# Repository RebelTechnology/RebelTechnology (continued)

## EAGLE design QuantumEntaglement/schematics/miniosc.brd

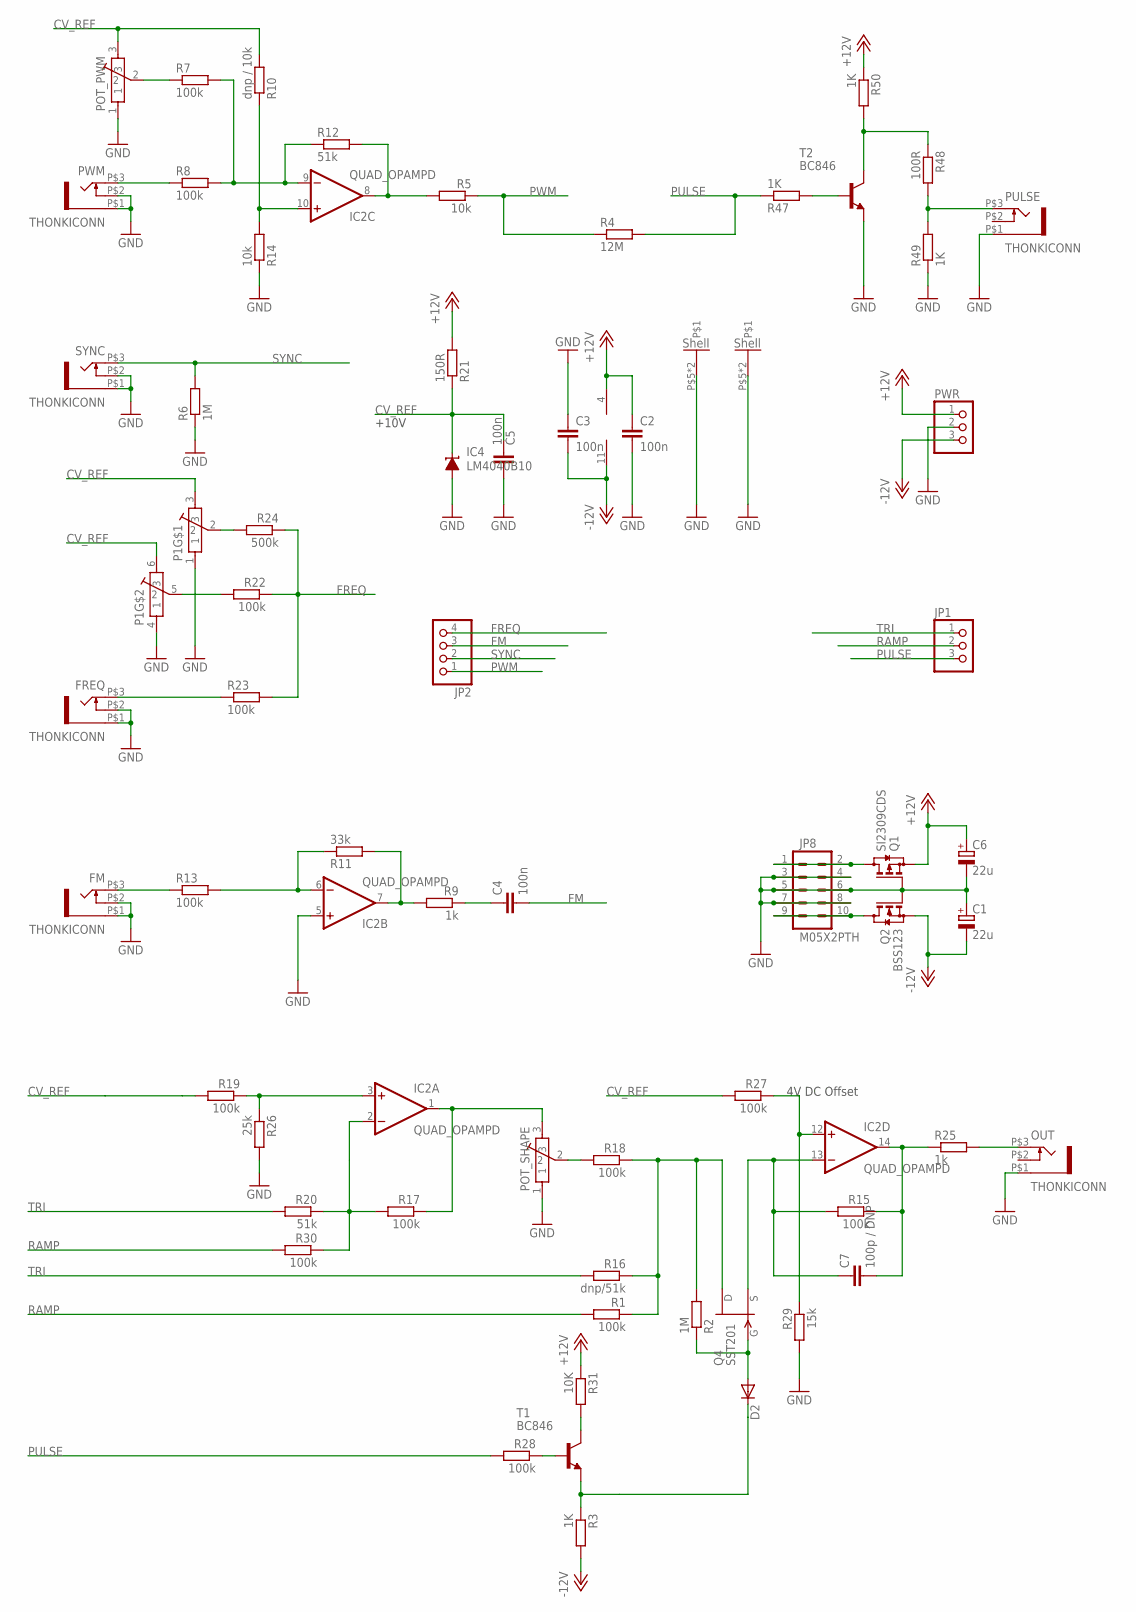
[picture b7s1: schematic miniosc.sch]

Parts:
C1, C6: 22u; CPOL-5
C2, C3, C4, C5: 100n; C0603
C7: 100p / DNP; C0603
D2: DIODE; DIODE-0805
FM: THONKICONN
FREQ: THONKICONN
IC2: QUAD_OPAMPD; SO14
IC4: LM4040B10; DBZ_R-PDSO-G3
JP1: PINHD-1X3; 1X03
JP2: PINHD-1X4; 1X04
JP8: M05X2PTH; AVR_ICSP
OUT: THONKICONN
P1: POT-BOURNS-PTD902
POT_PWM: POT-ALPS-RK09L1140
POT_SHAPE: POT-ALPS-RK09L1140
PULSE: THONKICONN
PWM: THONKICONN
PWR: PINHD-1X3; 1X03
Q1: SI2309CDS; SOT23
Q2: BSS123; SOT23
Q4: SST201; SOT23
R1, R7, R8, R13, R15, R17, R18, R19, R22, R23, R27, R28, R30: 100k; 0603
R2, R6: 1M; 0603
R3, R47, R49, R50: 1K; 0603
R4: 12M; 0603
R5, R14: 10k; 0603
R9, R25: 1k; 0603
R10: dnp / 10k; 0603
R11: 33k; 0603
R12, R20: 51k; 0603
R16: dnp/51k; 0603
R21: 150R; 0603
R24: 500k; 0603
R26: 25k; 0603
R29: 15k; 0603
R31: 10K; 0603
R48: 100R; 0603
SYNC: THONKICONN
T1, T2: BC846; SOT23

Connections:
+12V: C2.1, C6.+, IC2.4 (V+), PWR.1, Q1.2 (S), R21.2, R31.1, R50.1
-12V: C1.-, C3.2, IC2.11 (V-), PWR.3, Q2.2 (S), R3.2
CV_REF: C5.1, IC4.1 (C), P1.3, P1.6 (3), POT_PWM.3, R10.2, R19.2, R21.1, R27.2
FM: C4.2, JP2.3
FREQ: JP2.4, R22.1, R23.2, R24.1
GND: C1.+, C2.2, C3.1, C5.2, C6.-, FM.P$1 (5), FM.P$2 (4), FREQ.P$1 (5), FREQ.P$2 (4), IC2.5 (+IN), IC4.2 (A), JP8.3, JP8.4, JP8.5, JP8.6, JP8.7, JP8.8, OUT.P$1 (5), P1.1, P1.4 (1), POT_PWM.1, POT_PWM.P$5, POT_PWM.P$6, POT_SHAPE.1, POT_SHAPE.P$5, POT_SHAPE.P$6, PULSE.P$1 (5), PWM.P$1 (5), PWM.P$2 (4), PWR.2, Q1.1 (G), Q2.1 (G), R6.1, R14.1, R26.2, R29.2, R49.1, SYNC.P$1 (5), SYNC.P$2 (4), T2.2 (E)
unnamed: R31.2, T1.3 (C)
unnamed: PWM.P$3 (3), R8.1
unnamed: FREQ.P$3 (3), R23.1
unnamed: C7.1, IC2.13 (-IN), Q4.2 (S), R15.2
unnamed: IC2.9 (-IN), R7.2, R8.2, R12.1
unnamed: IC2.10 (+IN), R10.1, R14.2
unnamed: JP8.9, JP8.10, Q2.3 (D)
unnamed: P1.2, R24.2
unnamed: PULSE.P$3 (3), R48.2, R49.2
unnamed: IC2.1 (OUT), POT_SHAPE.3, R17.1
unnamed: JP8.1, JP8.2, Q1.3 (D)
unnamed: P1.5 (2), R22.2
unnamed: IC2.2 (-IN), R17.2, R20.1, R30.1
unnamed: C7.2, IC2.14 (OUT), R15.1, R25.1
unnamed: IC2.3 (+IN), R19.1, R26.1
unnamed: IC2.12 (+IN), R27.1, R29.1
unnamed: FM.P$3 (3), R13.1
unnamed: IC2.6 (-IN), R11.1, R13.2
unnamed: OUT.P$3 (3), R25.2
unnamed: IC2.7 (OUT), R9.2, R11.2
unnamed: C4.1, R9.1
unnamed: Q4.1 (D), R1.1, R2.2, R16.1, R18.1
unnamed: D2.C, R3.1, T1.2 (E)
unnamed: POT_PWM.2, R7.1
unnamed: IC2.8 (OUT), R5.2, R12.2
unnamed: R28.1, T1.1 (B)
unnamed: POT_SHAPE.2, R18.2
unnamed: D2.A, Q4.3 (G), R2.1
unnamed: R47.2, T2.1 (B)
unnamed: R48.1, R50.2, T2.3 (C)
PULSE: JP1.3, R4.2, R28.2, R47.1
PWM: JP2.1, R4.1, R5.1
RAMP: JP1.2, R1.2, R30.2
SYNC: JP2.2, R6.2, SYNC.P$3 (3)
TRI: JP1.1, R16.2, R20.2

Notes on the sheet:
+10V
4V DC Offset

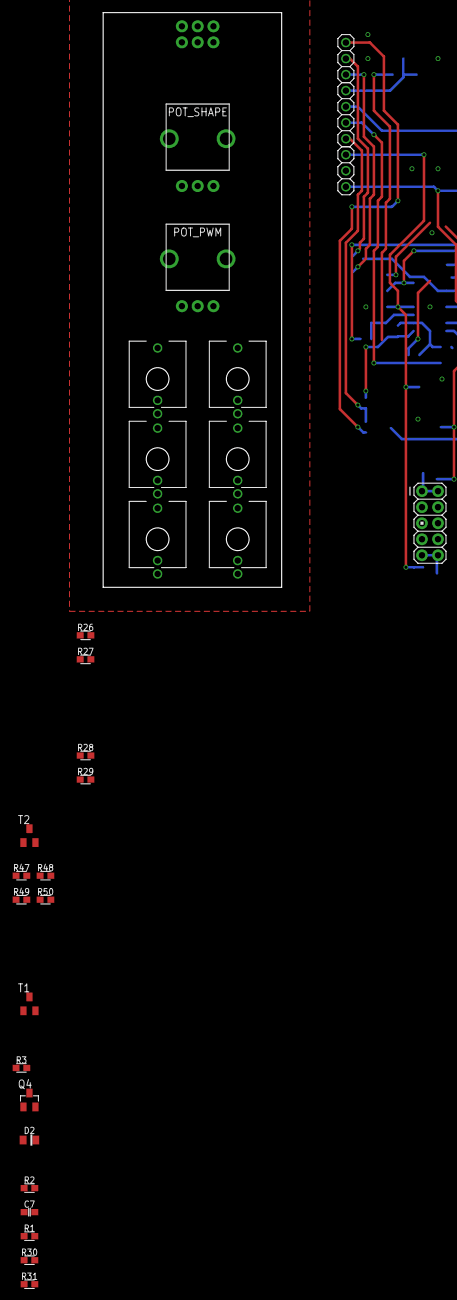
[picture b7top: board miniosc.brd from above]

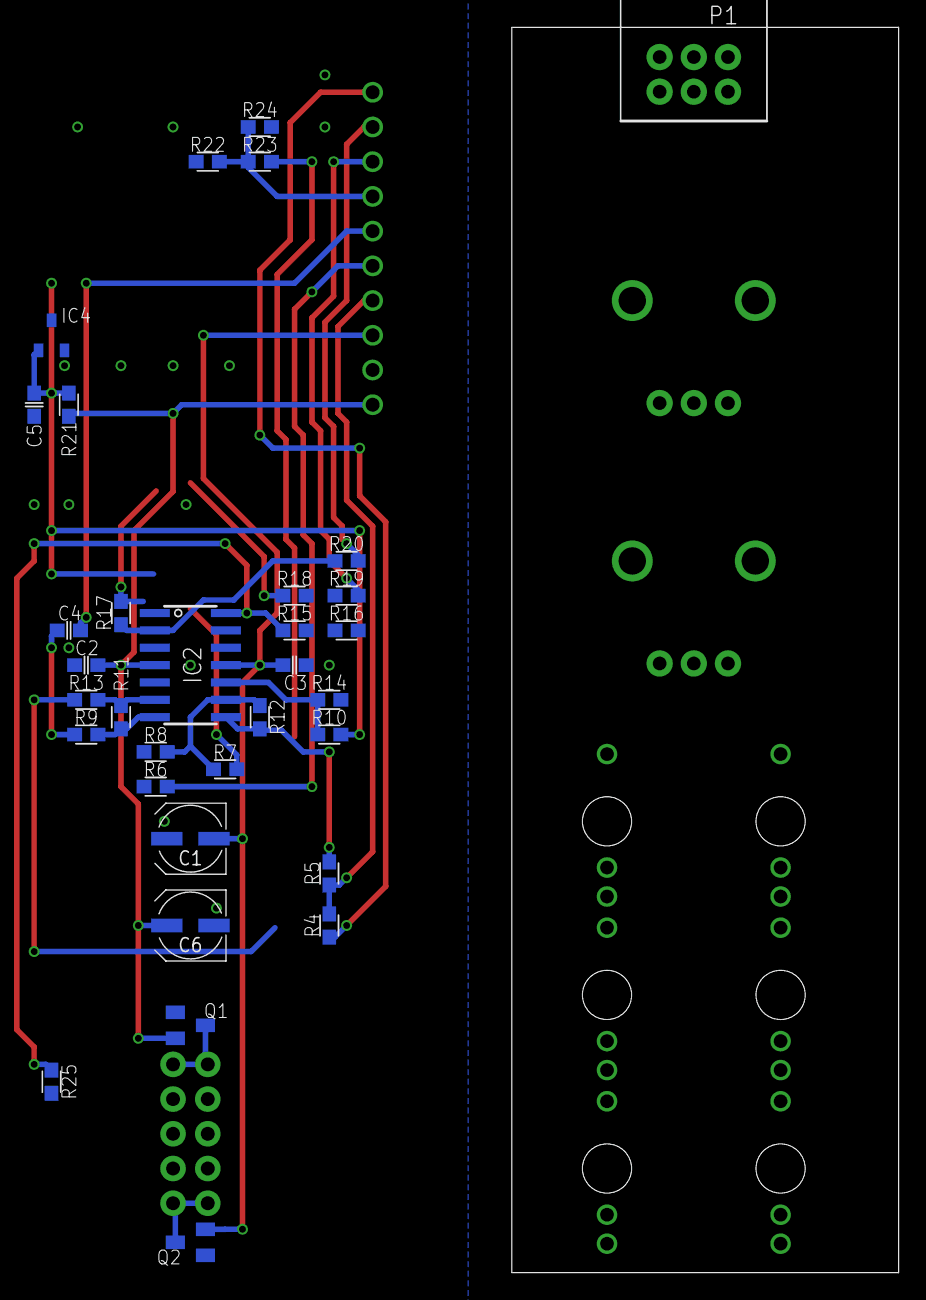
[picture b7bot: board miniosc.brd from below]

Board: 2 copper layers, 28.3 x 91.1 mm, 63 parts (33 on the bottom side), 41 nets.

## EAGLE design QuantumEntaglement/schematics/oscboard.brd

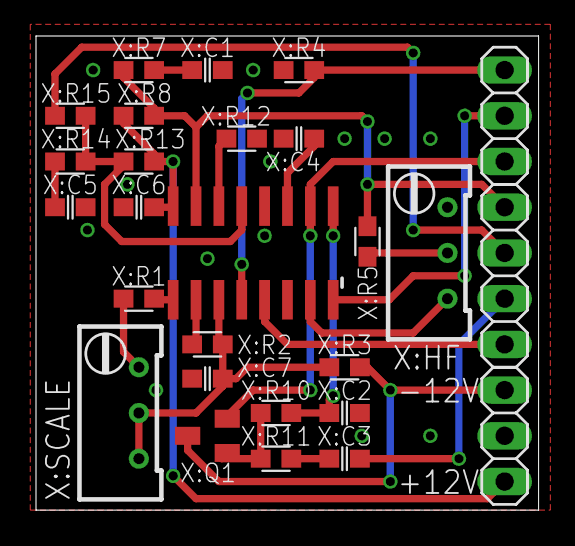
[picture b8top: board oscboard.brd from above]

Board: 2 copper layers, 27.9 x 26.3 mm, 27 parts (0 on the bottom side), 24 nets.

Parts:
JP1: 1X03
JP2: 1X04
PWR: 1X03
X:C1, X:C5: 10n; C0603
X:C2, X:C6, X:C7: 100n; C0603
X:C3: 200p; C0603
X:C4: 1n C0G; C0603
X:HF: 10k lin; RTRIM64W
X:IC1: V3340; SOIC16N
X:Q1: BC856; SOT23-BEC
X:R1: 20k; 0603
X:R2: 5k1; 0603
X:R3: 510R; 0603
X:R4, X:R5: 100k; 0603
X:R7, X:R14: 470R; 0603
X:R8: 370k; 0603
X:R10: 47k; 0603
X:R11: 10k; 0603
X:R12: 1k8; 0603
X:R13: 1M5; 0603
X:R15: 1M; 0603
X:SCALE: 10k lin; RTRIM64W

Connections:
+12V: PWR.1, X:C6.1, X:IC1.16, X:R8.1, X:R13.1
-12V: PWR.3, X:Q1.C, X:R3.2
FM: JP2.3, X:R15.1
FREQ: JP2.4, X:IC1.15, X:R5.1, X:R7.1, X:R8.2
GND: PWR.2, X:C1.2, X:C2.2, X:C4.2, X:C5.2, X:C6.2, X:C7.2, X:HF.3, X:IC1.12, X:R4.2, X:R12.1
PULSE: JP1.3, X:IC1.4, X:R4.1
PWM: JP2.1, X:IC1.5
RAMP: JP1.2, X:IC1.8
SYNC: JP2.2, X:C3.1
TRI: JP1.1, X:IC1.10, X:Q1.E
X:N$1: X:IC1.1, X:R1.1
X:N$2: X:R1.2, X:SCALE.3
X:N$3: X:HF.1, X:IC1.7
X:N$4: X:IC1.2, X:R2.1
X:N$5: X:C7.1, X:IC1.3, X:R2.2, X:R3.1, X:SCALE.1, X:SCALE.2
X:N$6: X:HF.2, X:R5.2
X:N$9: X:C1.1, X:R7.2
X:N$11: X:C2.1, X:IC1.9, X:R10.2
X:N$12: X:Q1.B, X:R10.1, X:R11.1
X:N$13: X:C3.2, X:R11.2
X:N$14: X:C4.1, X:IC1.11
X:N$16: X:IC1.14, X:R12.2
X:N$17: X:IC1.13, X:R13.2, X:R14.1, X:R15.2
X:N$18: X:C5.1, X:R14.2
